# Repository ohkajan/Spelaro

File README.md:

<h1 align="center">

</h1> 
<h4 align="center">
A super compact, ESP32-S3 powered optical TOSLINK transmitter with wireless streaming and an easy-to-use Android app!
</h4>
<div align="center">

</div>

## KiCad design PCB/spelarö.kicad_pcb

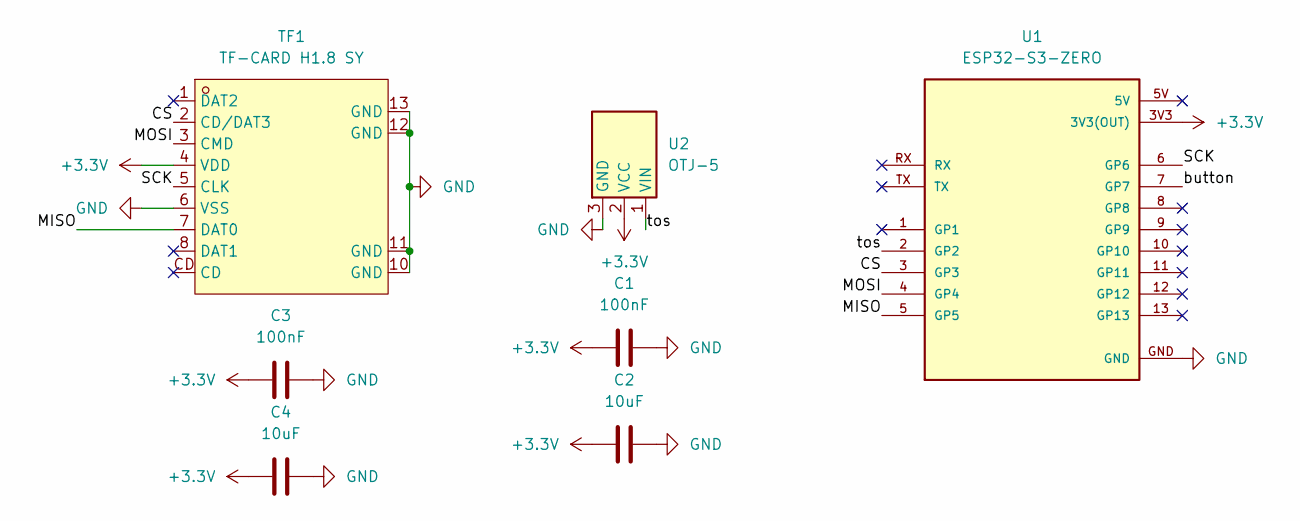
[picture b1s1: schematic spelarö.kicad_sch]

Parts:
C1, C3: 100nF; C_1206_3216Metric
C2, C4: 10uF; C_1206_3216Metric
TF1: TF-CARD H1.8 SY; TF-SMD_TF-012; MPN TF-CARD H1.8 SY; LCSC Part C7529391
U1: ESP32-S3-ZERO; MODULE_ESP32-S3-ZERO; PARTREV NA
U2: OTJ-5; toslink

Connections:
+3.3V: C1.1, C2.1, C3.1, C4.1, TF1.4 (VDD), U1.3V3 (3V3(OUT)), U2.2 (VCC)
/CS: TF1.2 (CD/DAT3), U1.3 (GP3)
/MISO: TF1.7 (DAT0), U1.5 (GP5)
/MOSI: TF1.3 (CMD), U1.4 (GP4)
/SCK: TF1.5 (CLK), U1.6 (GP6)
/button: U1.7 (GP7)
/tos: U1.2 (GP2), U2.1 (VIN)
GND: C1.2, C2.2, C3.2, C4.2, TF1.6 (VSS), TF1.10 (GND), TF1.11 (GND), TF1.12 (GND), TF1.13 (GND), U1.GND, U2.3 (GND)

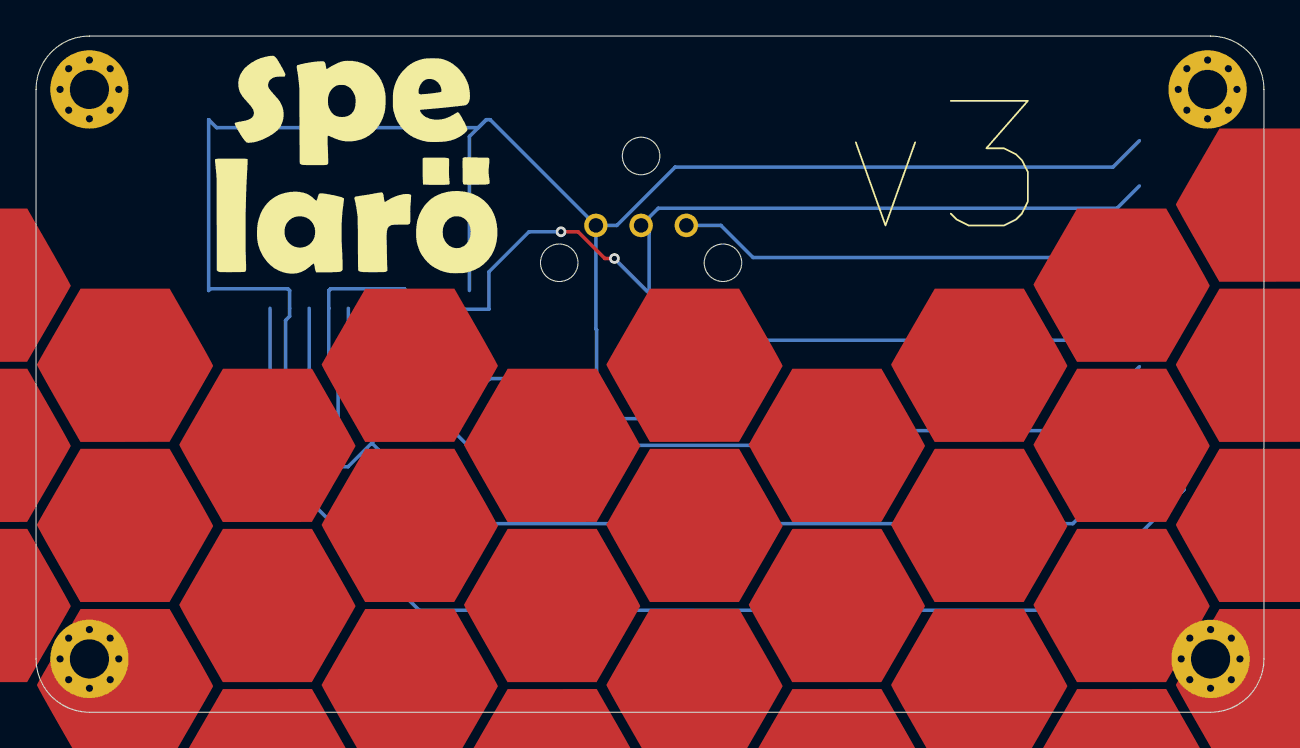
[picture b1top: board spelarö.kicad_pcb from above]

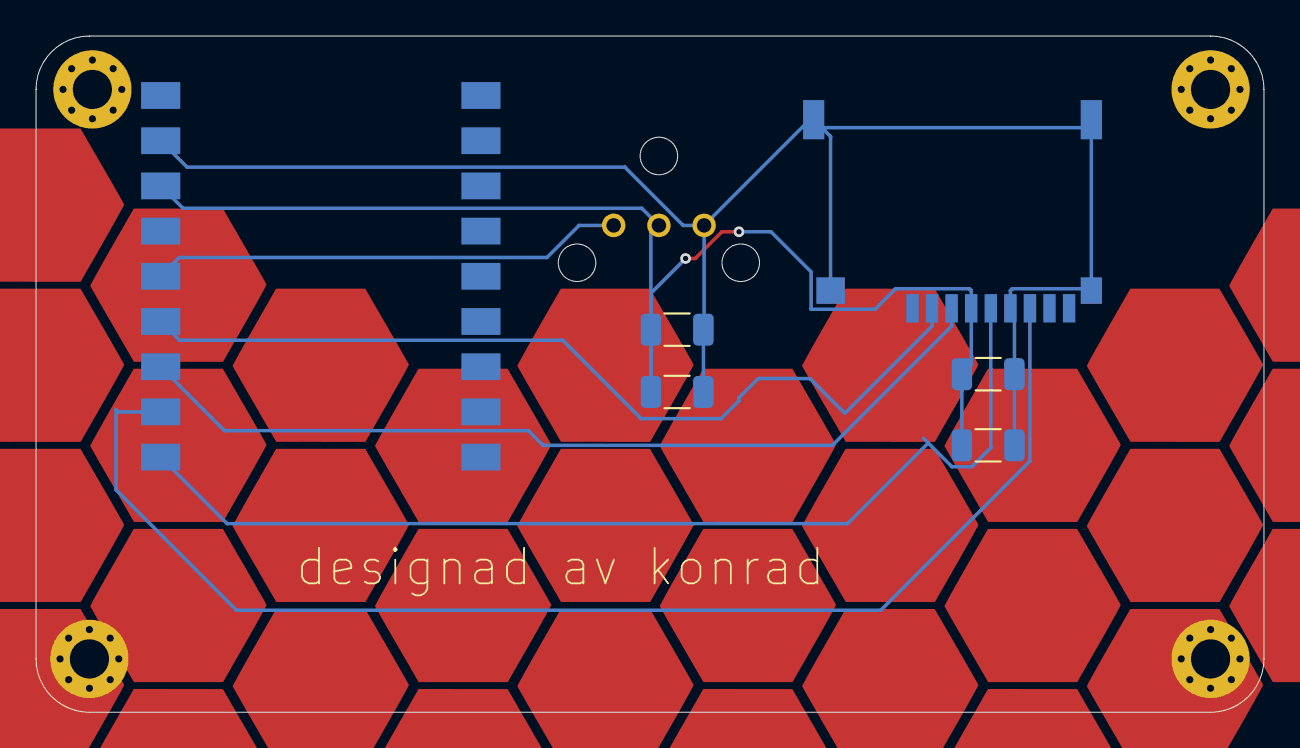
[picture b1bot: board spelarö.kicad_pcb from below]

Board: 2 copper layers, 69.0 x 38.0 mm, 7 parts (6 on the bottom side), 7 nets.

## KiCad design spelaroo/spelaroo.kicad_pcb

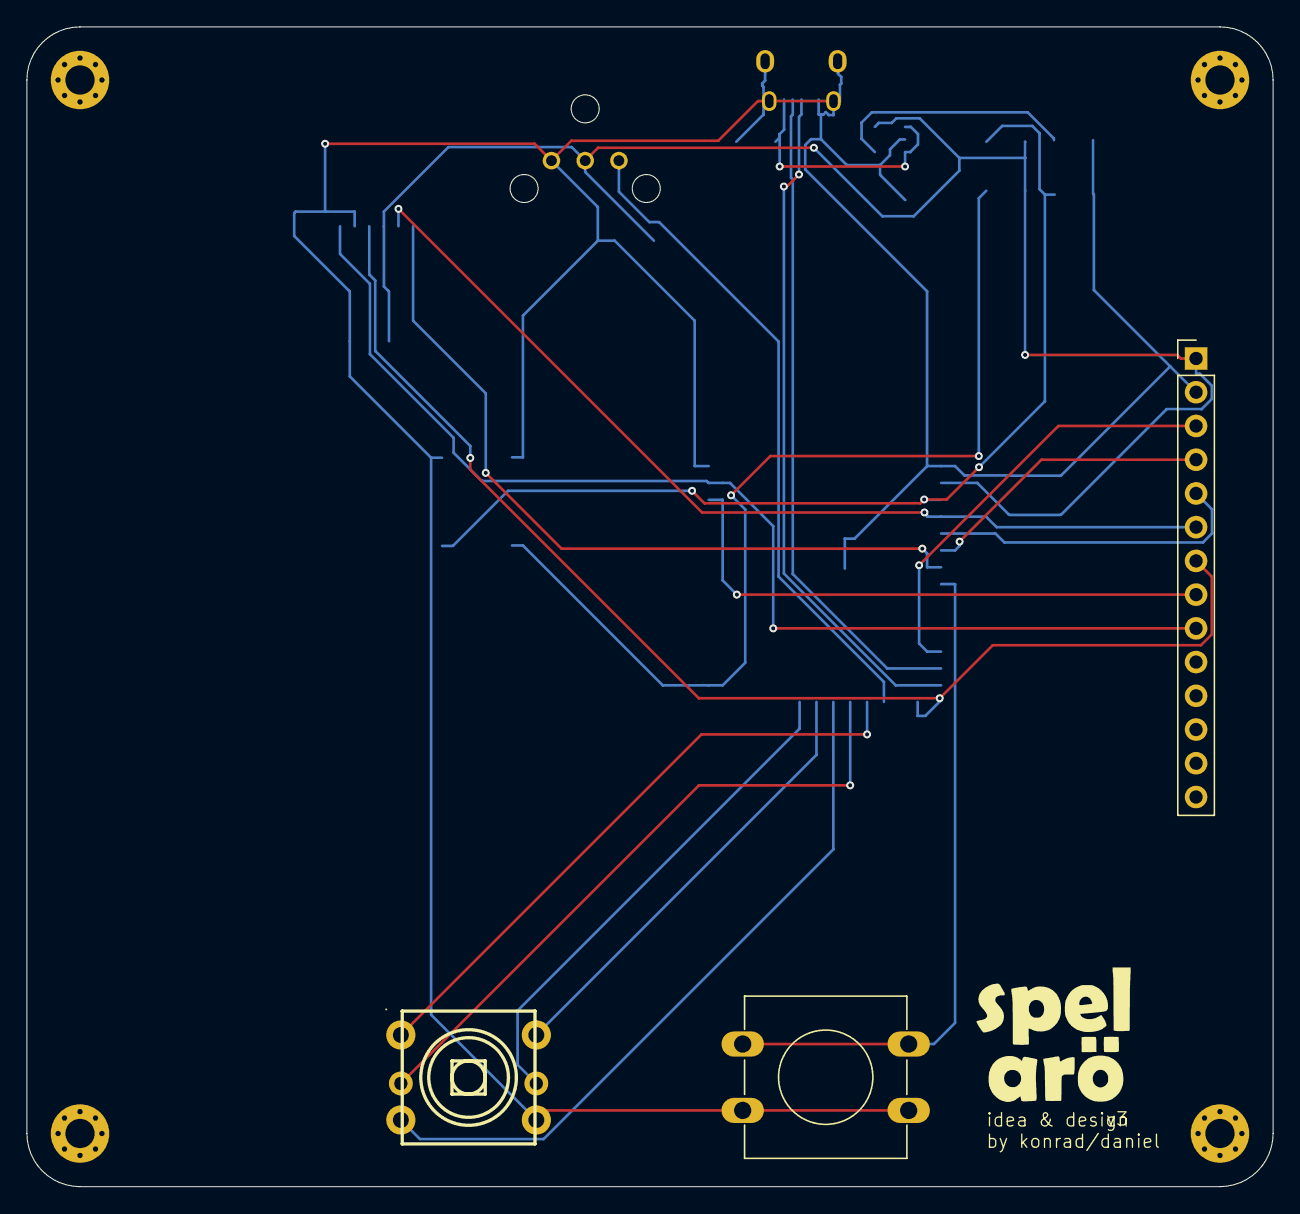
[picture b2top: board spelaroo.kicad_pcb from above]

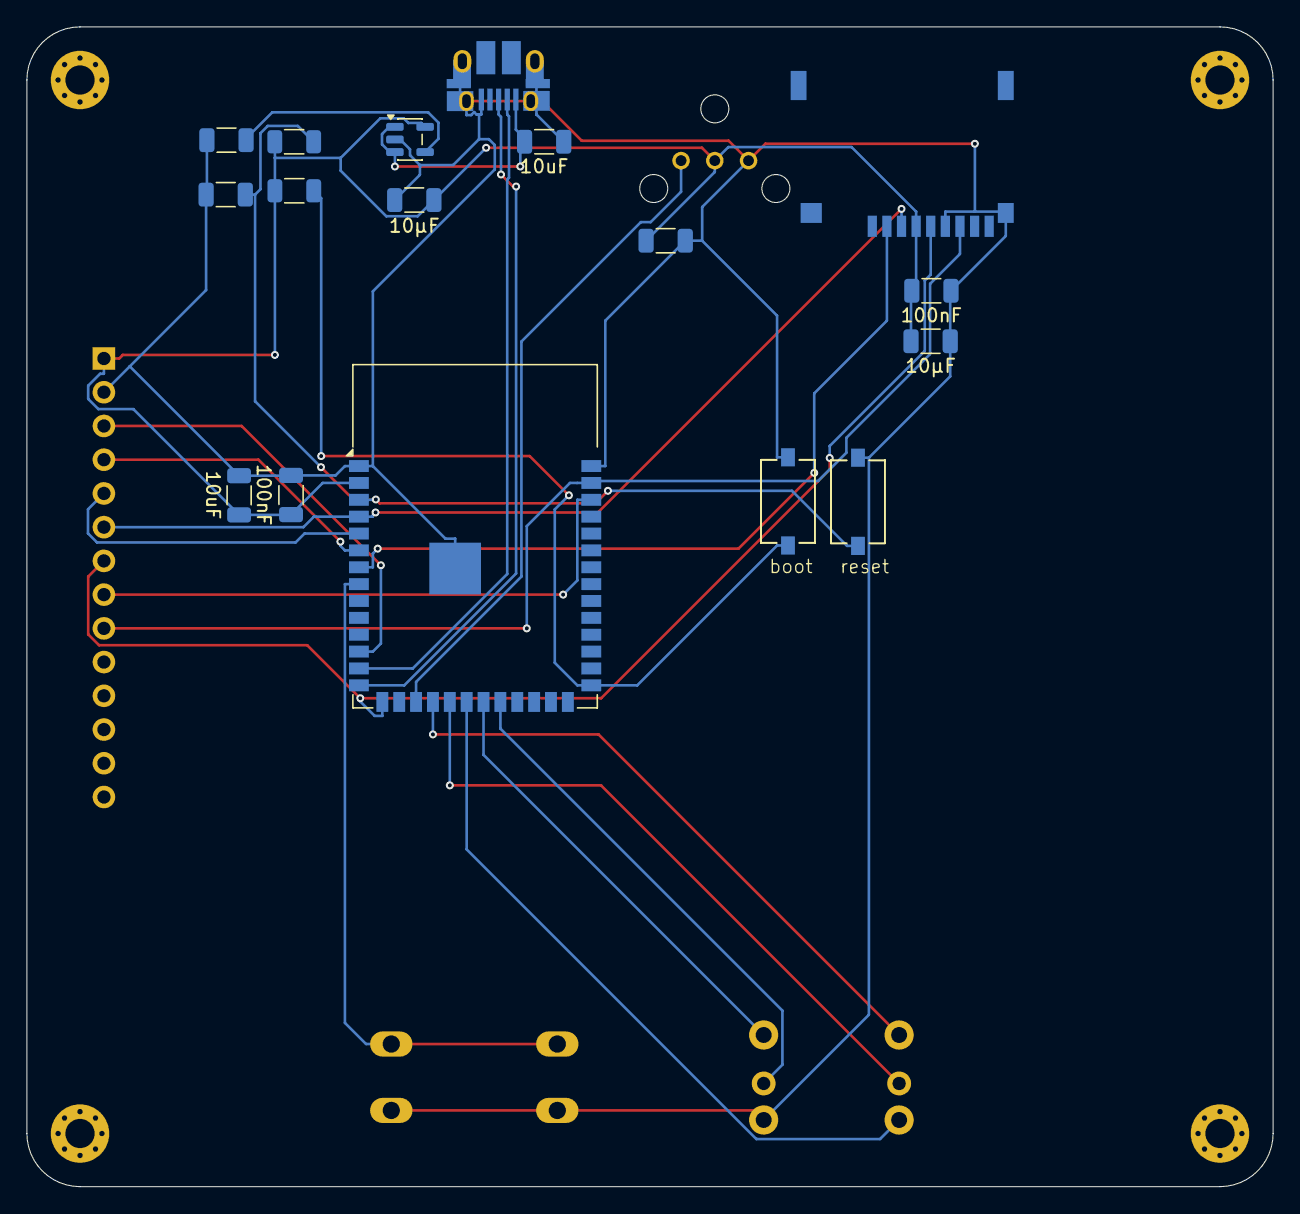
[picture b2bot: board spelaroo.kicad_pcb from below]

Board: 2 copper layers, 93.8 x 87.3 mm, 25 parts (17 on the bottom side), 23 nets.

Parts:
C1: 10nF; C_1206_3216Metric
C2, C3, C5, C9: 100nF; C_1206_3216Metric
C4, C6: 10uF; C_1206_3216Metric
C7, C8: 10µF; C_1206_3216Metric
J1: USB_B_Micro; USB_Micro-B_Amphenol_10103594-0001LF_Horizontal
J2: Conn_01x14_Pin; PinHeader_1x14_P2.54mm_Vertical
J3: Micro_SD_Card; TF-SMD_TF-012
M1, M2, M3, M4: MountingHole_2.2mm_M2_Pad_Via
R1, R2: 10k; R_1206_3216Metric
SW1, SW2: SW_Push; KSR221GLFS_CNK
SW3: K1-1506DN-01; SW-TH_K1-1506DN-01
SW4: SW_Push; SW_PUSH-12mm
U1: ESP32-S3-WROOM-1
U2: LP2985-3.3; SOT-23-5
U3: OTJ-5; toslink

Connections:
+3.3V: C3.1, C4.1, C5.1, C7.1, C8.1, C9.1, J2.1, J3.4 (VDD), R1.1, R2.1, U1.2 (3V3), U2.5 (VOUT), U3.2 (VCC)
+5V: C6.1, J1.1 (VBUS), U2.1 (VIN), U2.3 (ON/~OFF)
/1: SW3.1 (A), U1.18 (IO10)
/2: SW3.2 (B), U1.19 (IO11)
/3: SW3.3 (C), U1.20 (IO12)
/4: SW3.6 (CENTER), U1.21 (IO13)
/5: SW3.5 (D), U1.22 (IO14)
/6: SW4.1, U1.8 (IO15)
/CS_SD: J3.2 (DAT3/CD), U1.7 (IO7)
/CS_TFT: J2.3, U1.12 (IO8)
/DC: J2.5, U1.5 (IO5)
/LED: J2.8, U1.38 (IO2)
/MISO: J2.9, J3.7 (DAT0), U1.39 (IO1)
/MOSI: J2.6, J3.3 (CMD), U1.4 (IO4)
/RST_TFT: J2.4, U1.6 (IO6)
/SCK: J2.7, J3.5 (CLK), U1.15 (IO3)
/boot: R2.2, SW2.1, U1.27 (IO0)
/d+: J1.3 (D+), U1.14 (USB_D+)
/d-: J1.2 (D-), U1.13 (USB_D-)
/toslink: U1.17 (IO9), U3.1 (VIN)
GND: C1.2, C2.2, C3.2, C4.2, C5.2, C6.2, C7.2, C8.2, C9.2, J1.5 (GND), J1.SH (Shield), J2.2, J3.6 (VSS), J3.10 (SHIELD), SW1.2, SW2.2, SW3.4 (COMMON), SW4.2, U1.1 (GND), U1.40 (GND), U1.41 (GND), U2.2 (GND), U3.3 (GND)
unnamed: C2.1, R1.2, SW1.1, U1.3 (EN)
unnamed: C1.1, U2.4 (BP)

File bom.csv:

Designator,Footprint,Qty,Value,Link,Price (USD)
U1,ESP32-S3-WROOM-1,1,,https://www.electrokit.com/esp32-s3-wroom-1-mcu-modul-16mb-p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,"$7,60"
U2,Voltage Regulator,1,3.3V,https://www.electrokit.com/lp2985-33-sot-23-5-spanningsregul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,"$1,5"
U3,Toslink,1,,https://www.electrokit.com/toslink-optisk-sandare-pcb,"$2,9"
J1,Micro USB,1,,https://www.electrokit.com/usb-micro-b-kontakt-smd-pcb,"$1,1"
J2,Screen,1,,https://www.amazon.se/-/en/gp/product/B09Z29CGY1/ref=ox_sc_s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,"$13,58"
J3,Micro SD Reader,1,,https://www.electrokit.com/kontakt-microsd,$1.35
"SW1, SW2",Switch,,,https://www.electrokit.com/tryckknapp-pcb-smd-1-pol-ksr-2n,$3
SW3,5 way switch,1,,https://www.electrokit.com/navigeringsomkopplare-5-vags-med-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,"$2,15"
SW4,1 way switch,1,,https://www.electrokit.com/tryckknapp-pcb-12x12x5mm,$1.35
"C1, C3, C5, C7, C9",Capacitor,3,100nF,https://www.electrokit.com/kondensator-1206-x7r-100nf-10,$1.10
"C2, C4, C6, C8",Capacitor,,10uF,https://www.electrokit.com/kondensator-1206-x7r-10uf-1016v,$2.10
"R1, R2",Resistor,3,10k,https://www.electrokit.com/motstand-10kohm-0.25w-smd-1206,"$1,1"
PCB,-,5,-,https://jlcpcb.com,"$2,00"
Shipping,-,-,-,-,$35
Total,-,-,-,-,"$76"
